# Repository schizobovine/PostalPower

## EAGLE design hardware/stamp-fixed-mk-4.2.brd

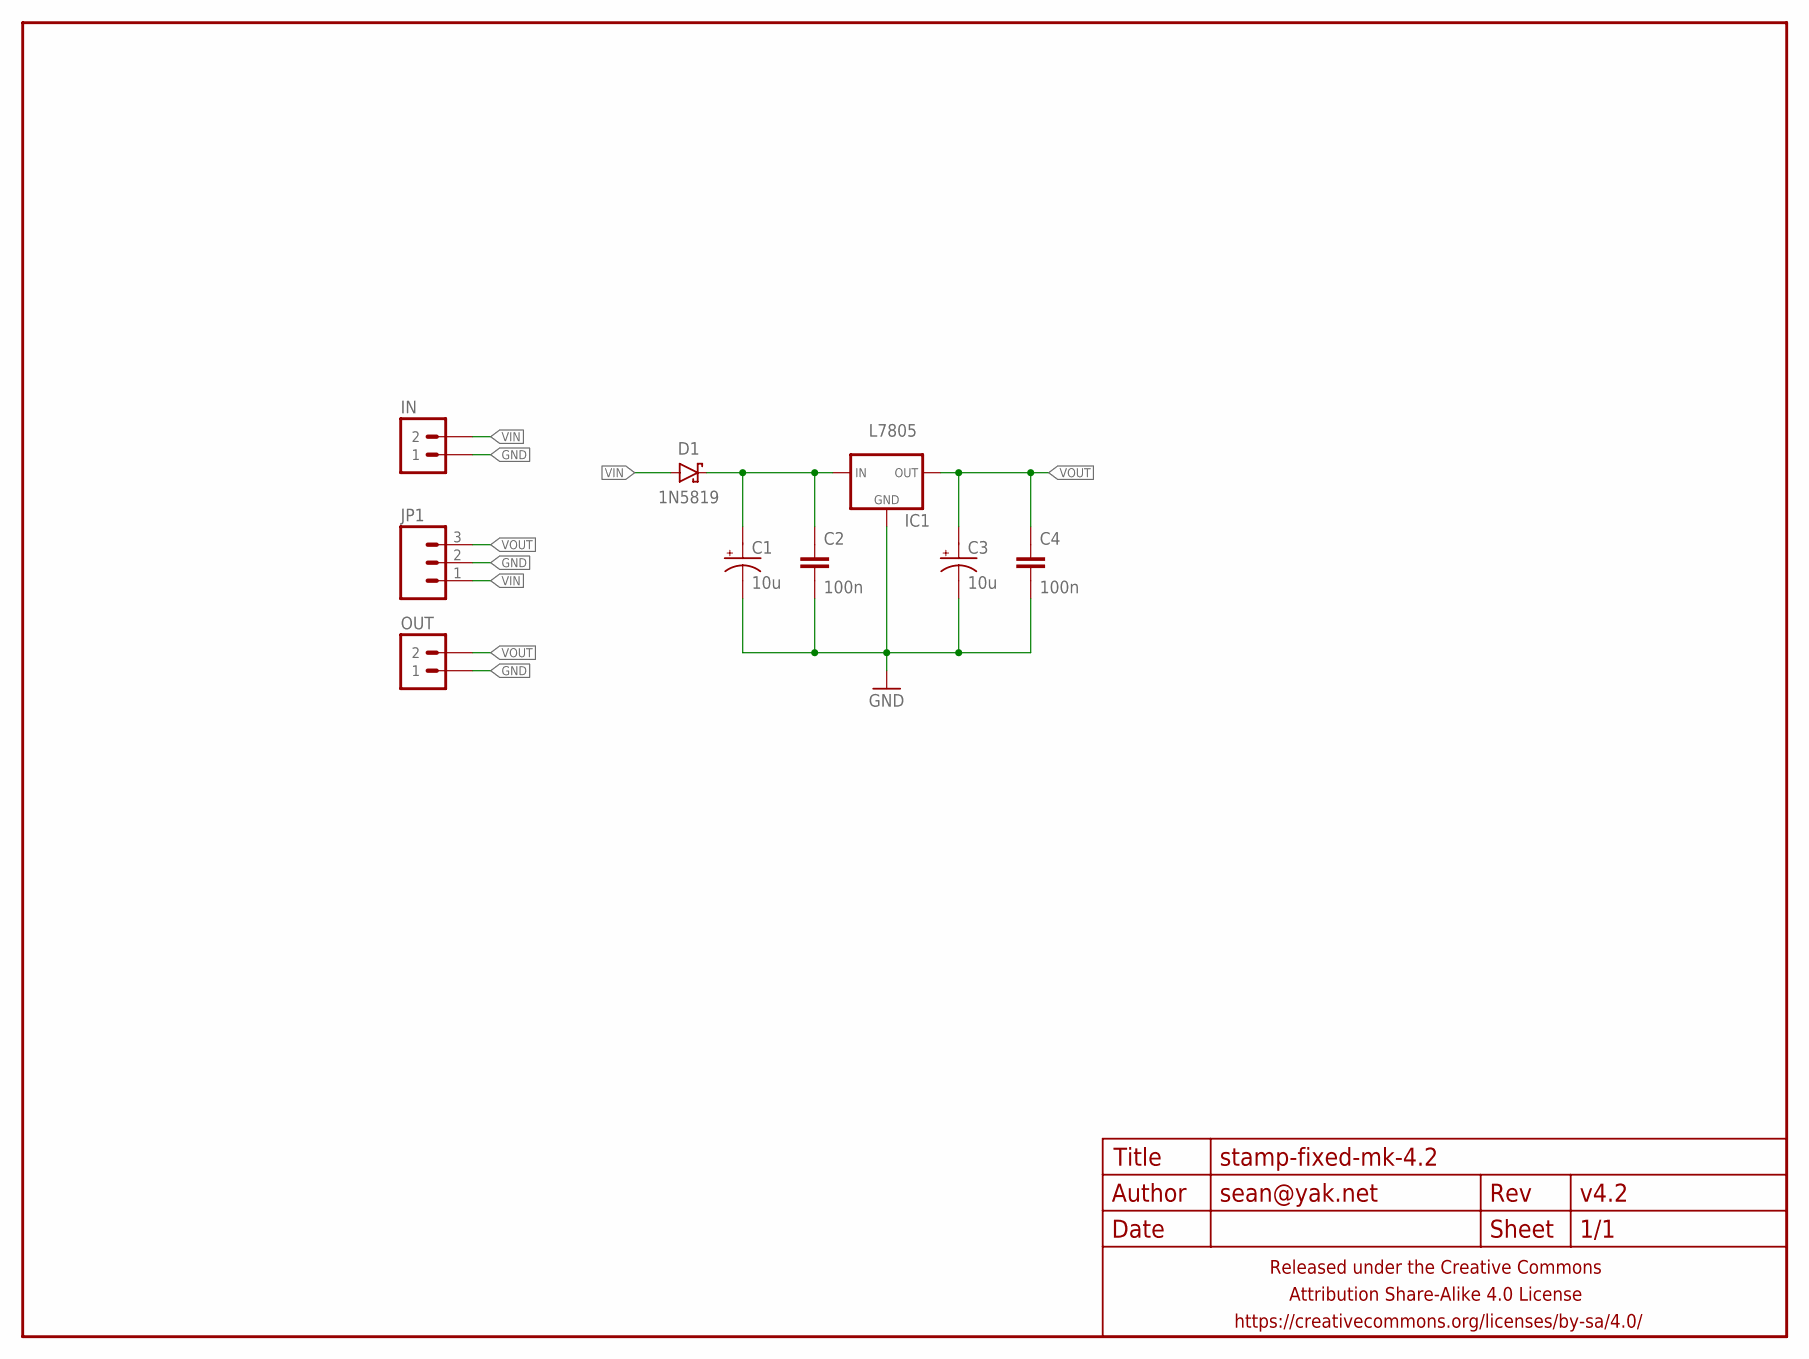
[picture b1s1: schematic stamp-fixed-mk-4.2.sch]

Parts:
C1, C3: 10u; E2,5-5
C2, C4: 100n; C025-024X044
D1: 1N5819; DIODE-SCHOTTKY-10.16MM
FRAME1: FRAME-LETTERNO_PACKAGE; DUMMY
IC1: L7805; TO220-IGO-THERMPAD
IN: M02PTH-CENTERED-R+; 1X02-CENTER-R+
JP1: M03PTH-CENTERED; 1X03-CENTERED
OUT: M02PTH-CENTERED-R+; 1X02-CENTER-R+

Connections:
GND: C1.-, C2.2, C3.-, C4.2, IC1.4 (GND), IC1.GND, IN.1, JP1.2, OUT.1
unnamed: C1.+, C2.1, D1.C, IC1.IN
VIN: D1.A, IN.2, JP1.1
VOUT: C3.+, C4.1, IC1.OUT, JP1.3, OUT.2

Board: 2 copper layers, 10 parts (0 on the bottom side), 4 nets, no tracks yet.

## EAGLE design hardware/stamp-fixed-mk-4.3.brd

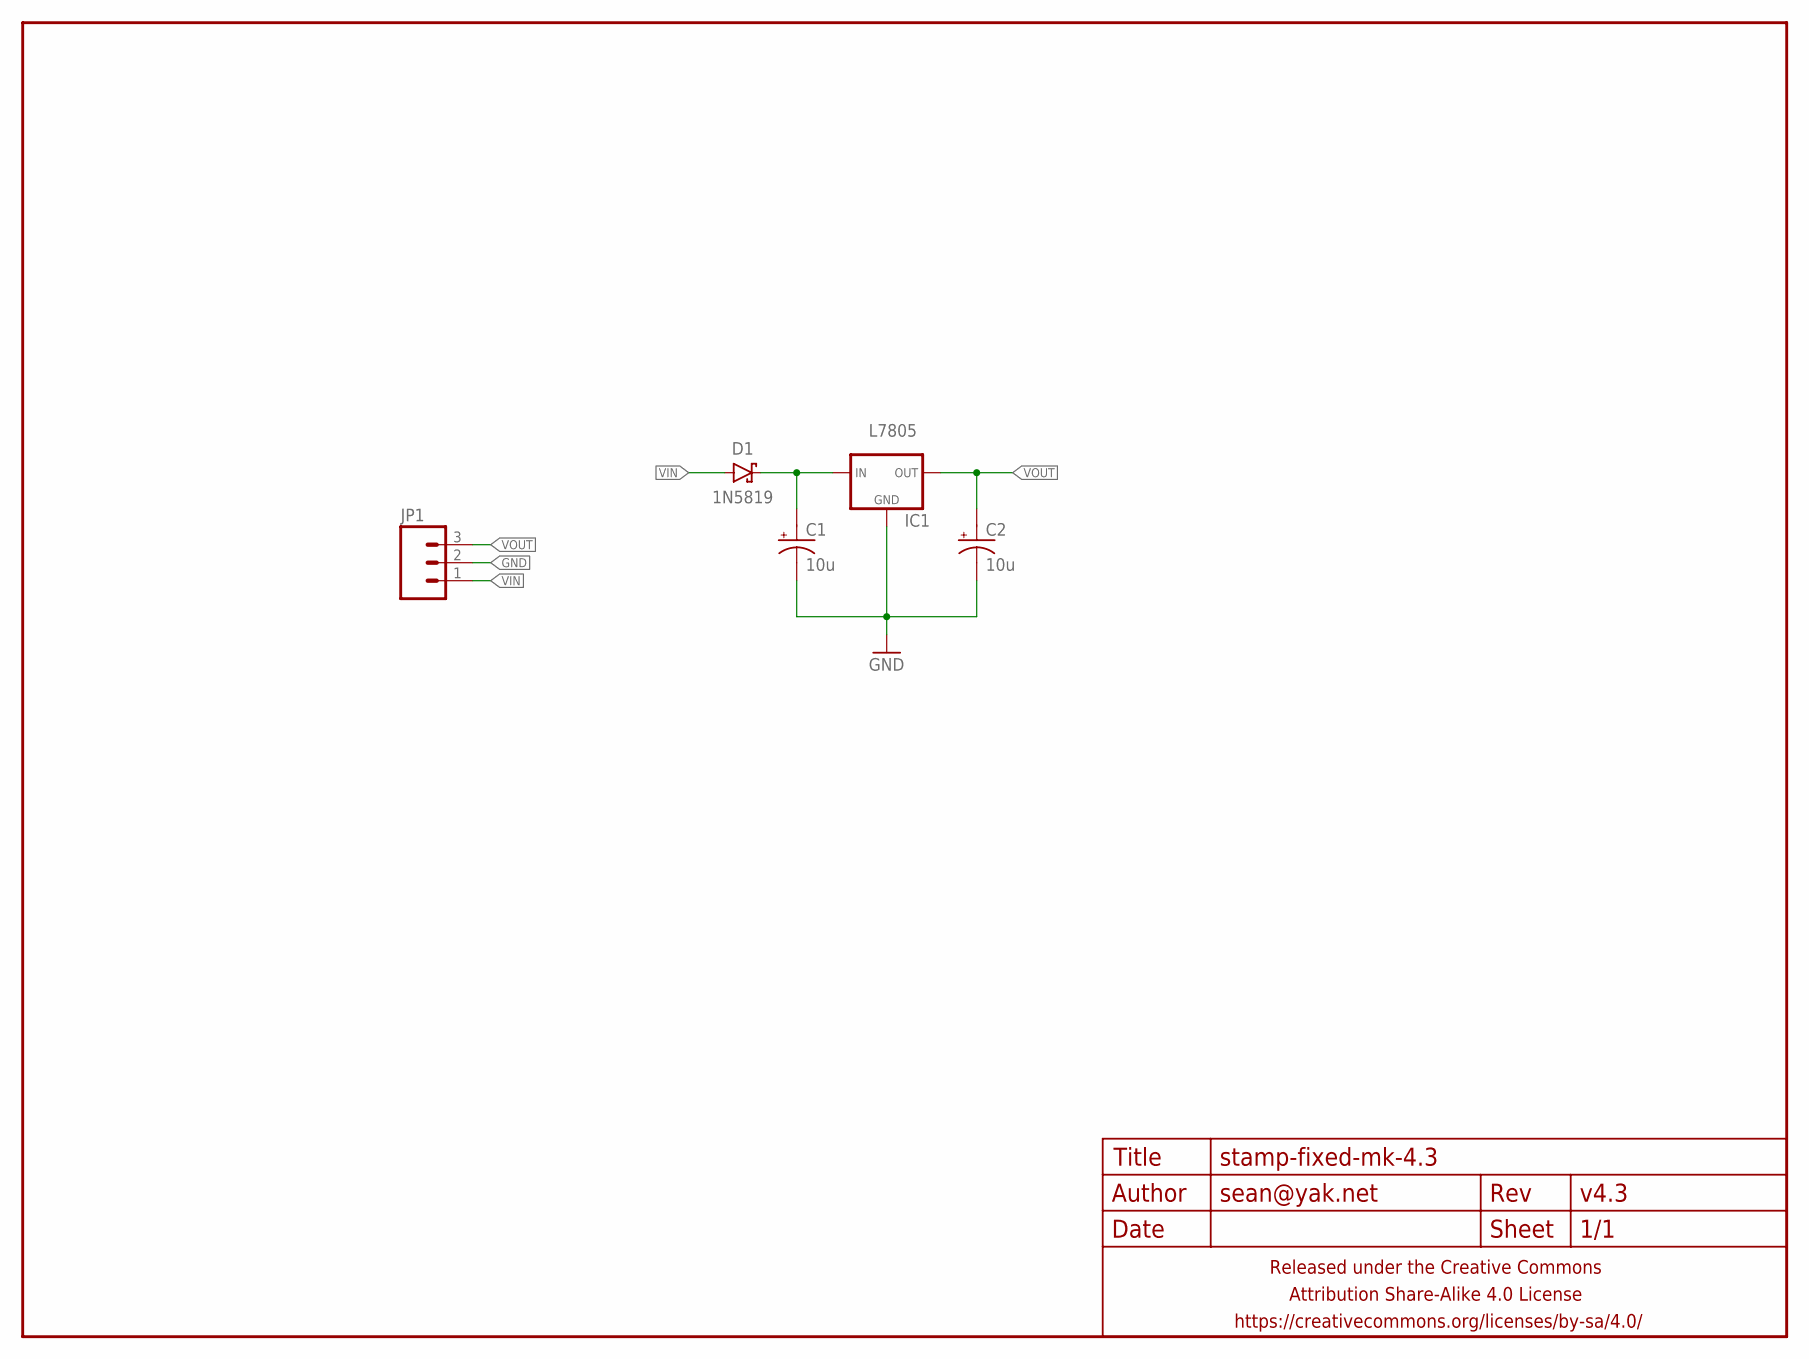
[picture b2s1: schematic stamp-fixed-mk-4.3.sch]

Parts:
C1, C2: 10u; E2,5-5
D1: 1N5819; DIODE-SCHOTTKY-10.16MM
FRAME1: FRAME-LETTERNO_PACKAGE; DUMMY
IC1: L7805; TO220-IGO-THERMPAD
JP1: M03PTH-CENTERED; 1X03-CENTERED

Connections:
GND: C1.-, C2.-, IC1.4 (GND), IC1.GND, JP1.2
unnamed: C1.+, D1.C, IC1.IN
VIN: D1.A, JP1.1
VOUT: C2.+, IC1.OUT, JP1.3

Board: 2 copper layers, 6 parts (0 on the bottom side), 4 nets, no tracks yet.

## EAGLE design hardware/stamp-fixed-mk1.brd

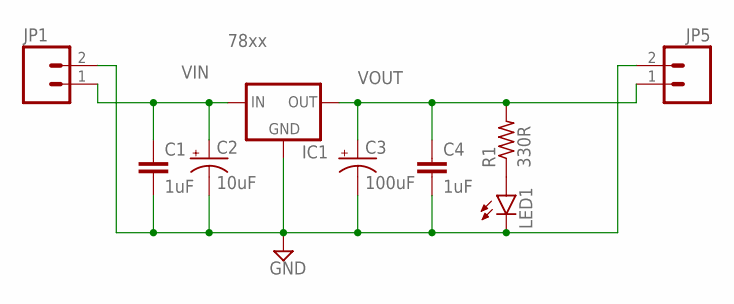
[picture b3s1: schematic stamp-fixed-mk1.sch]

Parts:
C1, C4: 1uF; C025-024X044
C2: 10uF; E2,5-6
C3: 100uF; E2,5-6
IC1: 78xx; TO-220-SIDE-THERM
JP1, JP5: M02JST-PTH-2; JST-2-PTH
LED1: LED3MM
R1: 330R; AXIAL-PTH-5.08MM

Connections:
GND: C1.2, C2.-, C3.-, C4.2, IC1.GND, IC1.GND@1 (GND), IC1.GND@2 (GND), IC1.GND@3 (GND), IC1.GND@4 (GND), IC1.GND@5 (GND), IC1.GND@6 (GND), IC1.GND@7 (GND), IC1.GND@8 (GND), IC1.GND@9 (GND), IC1.GND@10 (GND), IC1.GND@11 (GND), IC1.GND@12 (GND), IC1.GND@13 (GND), IC1.GND@14 (GND), IC1.GND@15 (GND), IC1.GND@16 (GND), IC1.GND@17 (GND), IC1.GND@18 (GND), IC1.GND@19 (GND), IC1.GND@20 (GND), IC1.GND@21 (GND), IC1.GND@22 (GND), IC1.GND@23 (GND), IC1.GND@24 (GND), IC1.GND@25 (GND), IC1.GND@26 (GND), IC1.GND@27 (GND), IC1.GND@28 (GND), IC1.GND@29 (GND), IC1.GND@30 (GND), IC1.GND@31 (GND), IC1.GND@32 (GND), IC1.GND@33 (GND), IC1.GND@34 (GND), IC1.GND@35 (GND), IC1.GND@36 (GND), IC1.GND@37 (GND), IC1.GND@38 (GND), IC1.GND@39 (GND), IC1.GND@40 (GND), IC1.GND@41 (GND), IC1.GND@42 (GND), IC1.GND@43 (GND), IC1.GND@44 (GND), IC1.GND@45 (GND), IC1.GND@46 (GND), IC1.GND@47 (GND), IC1.GND@48 (GND), IC1.GND@49 (GND), IC1.GND@50 (GND), IC1.GND@51 (GND), IC1.GND@52 (GND), IC1.GND@53 (GND), IC1.GND@54 (GND), JP1.2, JP5.2, LED1.K (C)
unnamed: LED1.A, R1.P$1 (1)
VIN: C1.1, C2.+, IC1.IN, JP1.1
VOUT: C3.+, C4.1, IC1.OUT, JP5.1, R1.P$2 (2)

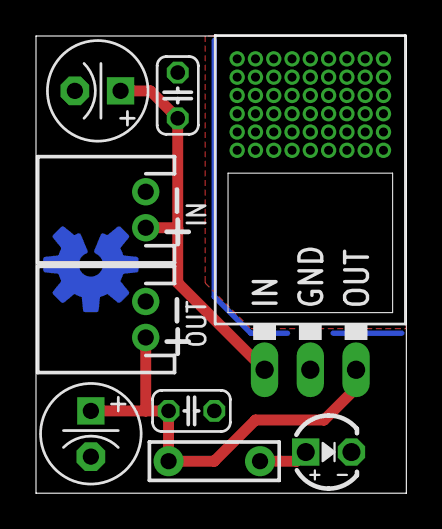
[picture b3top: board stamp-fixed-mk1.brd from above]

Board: 2 copper layers, 20.6 x 25.4 mm, 11 parts (1 on the bottom side), 4 nets.

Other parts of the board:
U$1: OSHWLOGO_BOT_0.2_A
U$2: COW

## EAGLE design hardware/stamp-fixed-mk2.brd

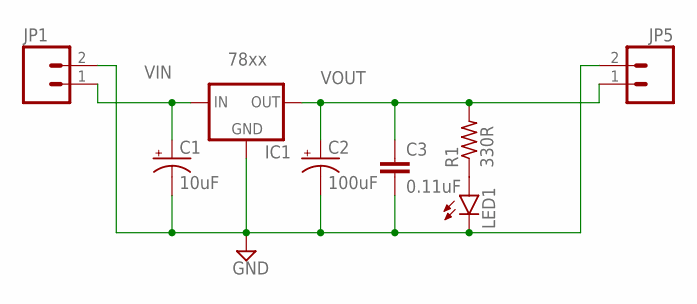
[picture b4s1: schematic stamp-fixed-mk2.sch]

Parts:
C1: 10uF; E2,5-6
C2: 100uF; E2,5-6
C3: 0.11uF; C025-024X044
IC1: 78xx; TO-220-SIDE-THERM
JP1, JP5: M02JST-PTH-2; JST-2-PTH
LED1: LED3MM
R1: 330R; RESISTOR-AXIAL-PTH-5.08MM

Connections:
GND: C1.-, C2.-, C3.2, IC1.GND, IC1.GND@1 (GND), IC1.GND@2 (GND), IC1.GND@3 (GND), IC1.GND@4 (GND), IC1.GND@5 (GND), IC1.GND@6 (GND), IC1.GND@7 (GND), IC1.GND@8 (GND), IC1.GND@9 (GND), IC1.GND@10 (GND), IC1.GND@11 (GND), IC1.GND@12 (GND), IC1.GND@13 (GND), IC1.GND@14 (GND), IC1.GND@15 (GND), IC1.GND@16 (GND), IC1.GND@17 (GND), IC1.GND@18 (GND), IC1.GND@19 (GND), IC1.GND@20 (GND), IC1.GND@21 (GND), IC1.GND@22 (GND), IC1.GND@23 (GND), IC1.GND@24 (GND), IC1.GND@25 (GND), IC1.GND@26 (GND), IC1.GND@27 (GND), JP1.2, JP5.2, LED1.K (C)
unnamed: LED1.A, R1.P$1 (1)
VIN: C1.+, IC1.IN, JP1.1
VOUT: C2.+, C3.1, IC1.OUT, JP5.1, R1.P$2 (2)

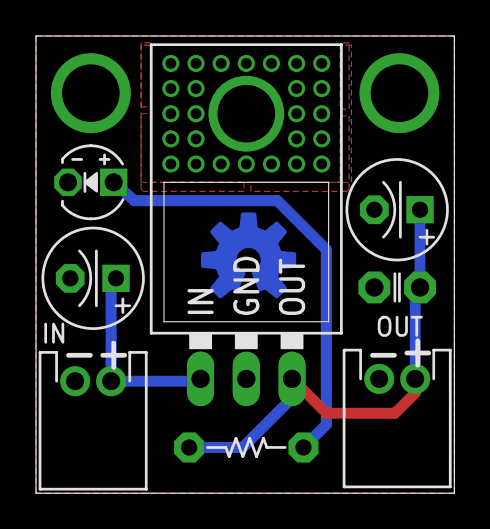
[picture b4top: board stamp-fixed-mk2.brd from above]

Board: 2 copper layers, 23.2 x 25.4 mm, 9 parts (0 on the bottom side), 4 nets.

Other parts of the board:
U$1: OSHWLOGO_BOT_0.2_A

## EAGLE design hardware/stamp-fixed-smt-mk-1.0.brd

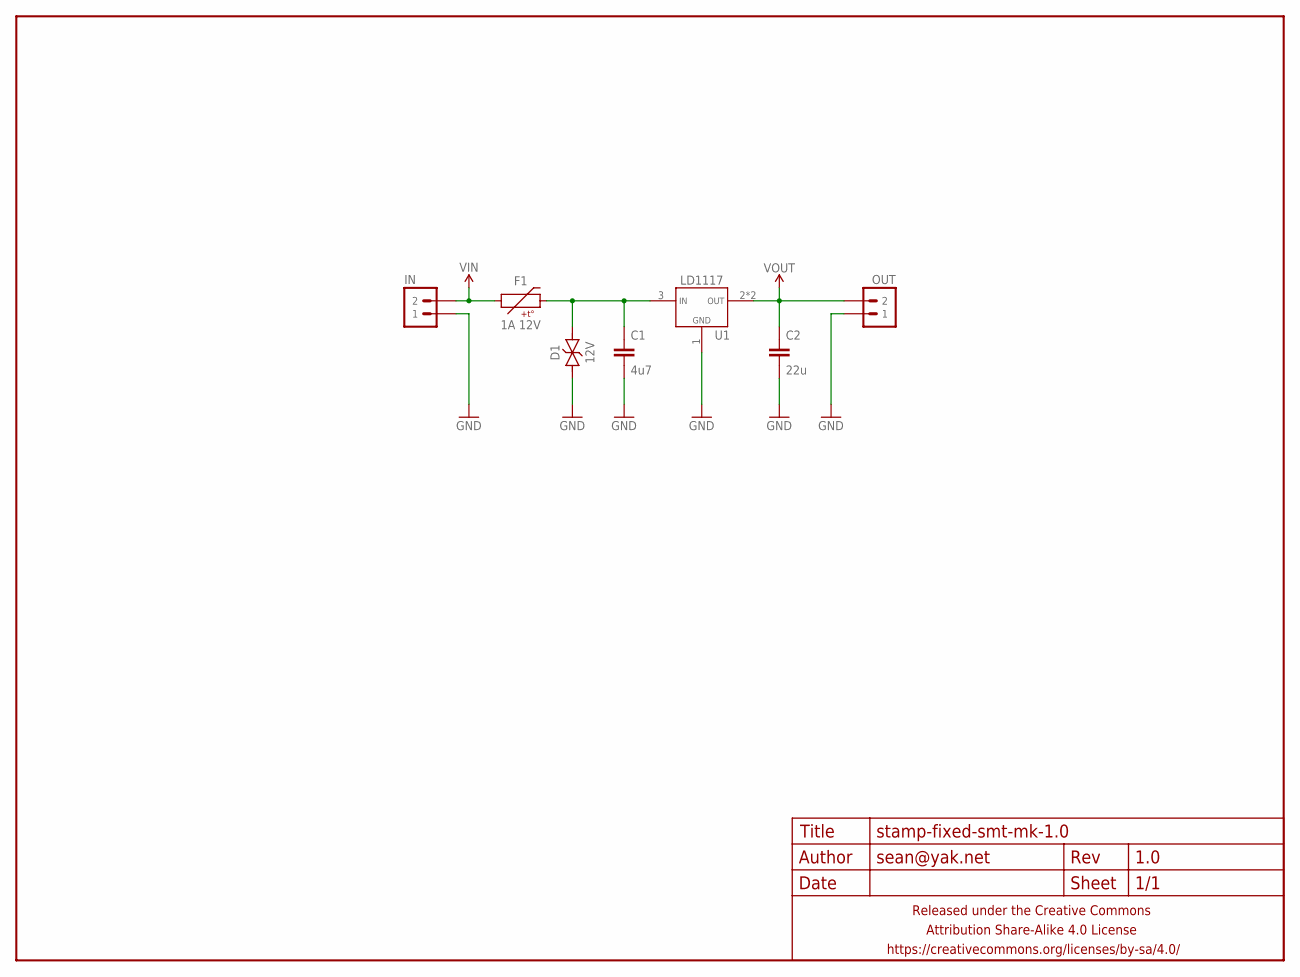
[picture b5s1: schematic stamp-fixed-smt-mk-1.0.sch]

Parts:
C1: 4u7; C0805-TIGHTER
C2: 22u; C0805-TIGHTER
D1: 12V; SOD323-TVS-BIDIR
F1: 1A 12V; PTC-1206
FRAME1: FRAME-LETTERNO_PACKAGE; DUMMY
IN: M02PTH-CENTERED-R+; 1X02-CENTER-R+
OUT: M02PTH-CENTERED-R+; 1X02-CENTER-R+
U1: LD1117; SOT223

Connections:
GND: C1.2, C2.2, D1.A (1), IN.1, OUT.1, U1.1 (GND)
unnamed: C1.1, D1.C (2), F1.2, U1.3 (VIN)
VIN: F1.1, IN.2
VOUT: C2.1, OUT.2, U1.2 (VOUT), U1.4 (VOUT)

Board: 2 copper layers, 8 parts (0 on the bottom side), 4 nets, no tracks yet.

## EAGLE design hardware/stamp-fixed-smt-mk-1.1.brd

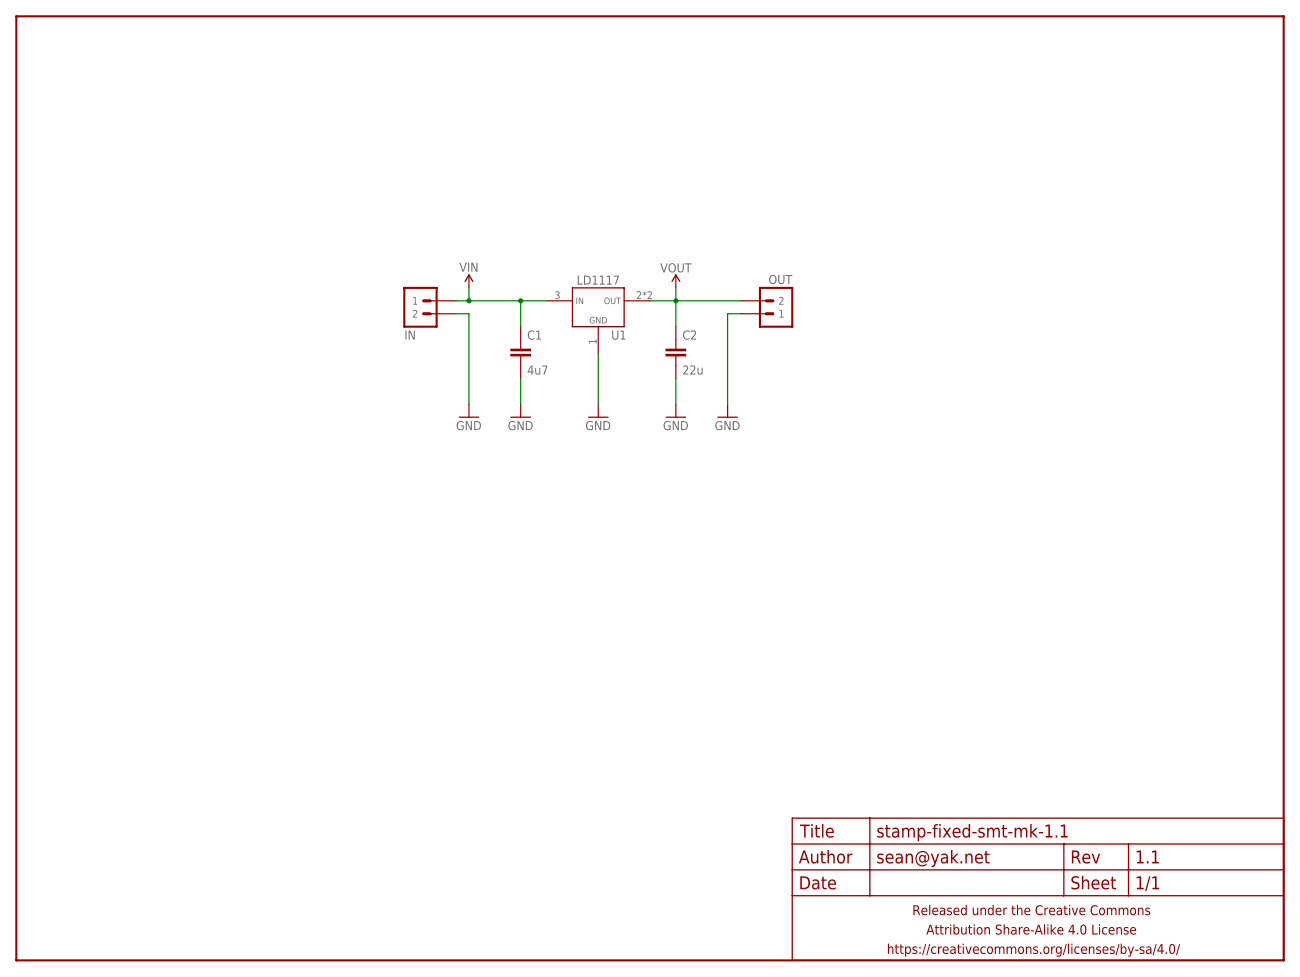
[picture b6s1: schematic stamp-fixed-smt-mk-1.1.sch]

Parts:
C1: 4u7; C0805-TIGHTER
C2: 22u; C0805-TIGHTER
FRAME1: FRAME-LETTERNO_PACKAGE; DUMMY
IN: M02PTH-CENTERED-L+; 1X02-CENTER-L+
OUT: M02PTH-CENTERED-R+; 1X02-CENTER-R+
U1: LD1117; SOT223

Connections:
GND: C1.2, C2.2, IN.2, OUT.1, U1.1 (GND)
VIN: C1.1, IN.1, U1.3 (VIN)
VOUT: C2.1, OUT.2, U1.2 (VOUT), U1.4 (VOUT)

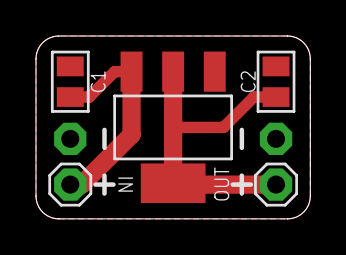
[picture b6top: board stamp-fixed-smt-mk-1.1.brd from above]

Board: 2 copper layers, 15.2 x 10.2 mm, 6 parts (0 on the bottom side), 3 nets.

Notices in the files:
parts and their libraries:
A_butts: Released under the Creative Commons Attribution Share-Alike 4.0 License
A_butts: https://creativecommons.org/licenses/by-sa/4.0
A_butts: Released under the Creative Commons
